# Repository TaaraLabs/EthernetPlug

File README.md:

Ethernet Plug
=============

[WebSite](https://taaralabs.eu/pe1)

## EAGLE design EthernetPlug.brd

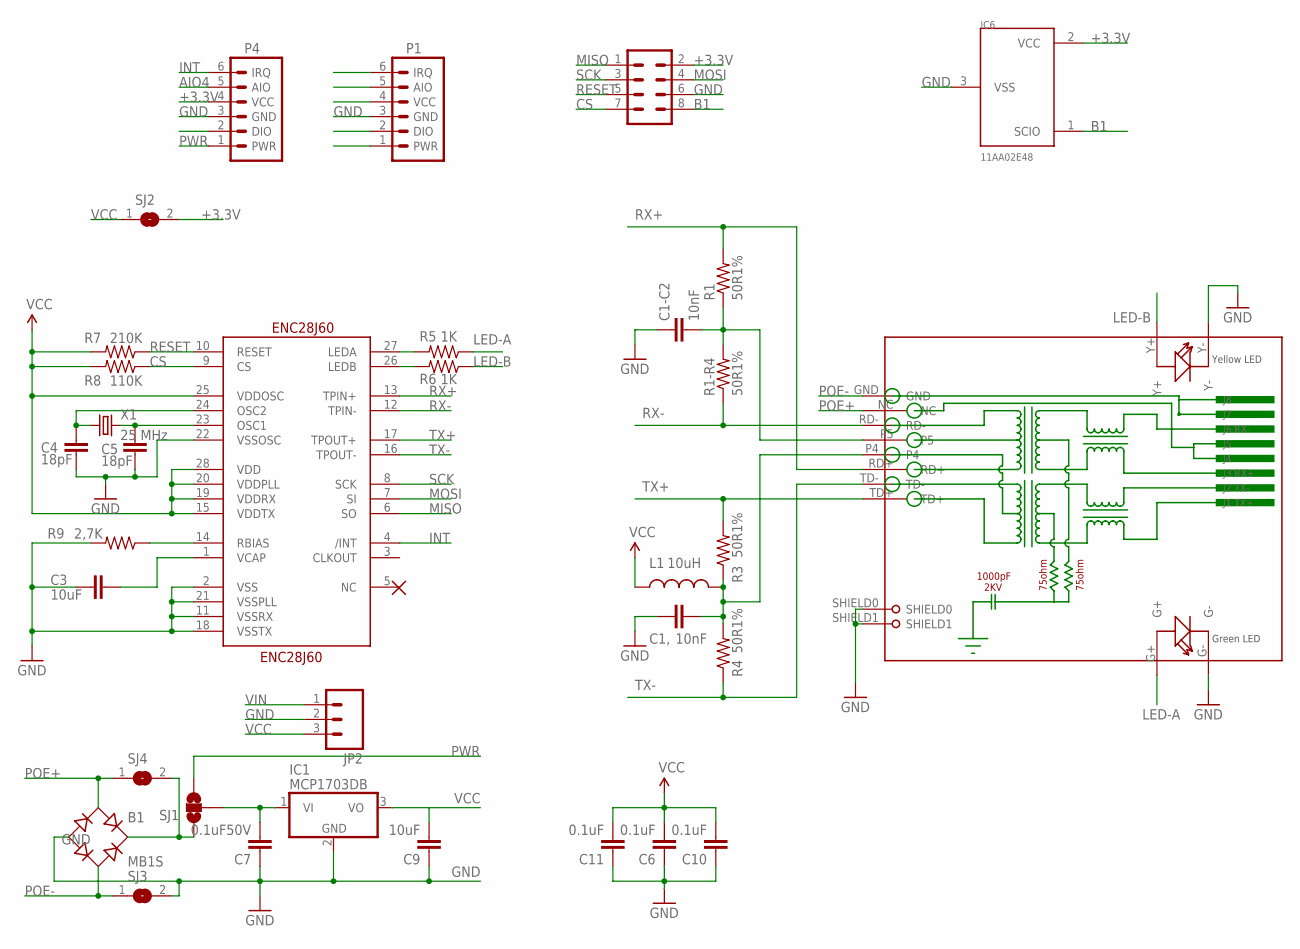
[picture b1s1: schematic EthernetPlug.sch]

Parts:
B1: MB1S; SOIC-4
C1,, C1-C2: 10nF; 0603-CAP
C3, C9: 10uF; 0603-CAP
C4, C5: 18pF; 0603-CAP
C6, C10, C11: 0.1uF; 0603-CAP
C7: 0.1uF50V; 0603-CAP
ENC28J60: ENC28J60; SSOP28DB
IC1: MCP1703DB; SOT223
IC6: 11AA02E48; SOT23
ISP: MA04-2
JP2: M03PTH; 1X03
L1: 10uH; 0603
P1, P4: JEEPORT-FEMALE; 1X06_FEMALE_LOCK.010
R1, R1-R4, R3, R4: 50R1%; 0603-RES
R5, R6: 1K; 0603-RES
R7: 210K; 0603-RES
R8: 110K; 0603-RES
R9: 2,7K; 0603-RES
RJ1: HLJ-6115ANL; HR911105A
SJ1: SOLDERJUMPER_2WAYT; SJ_2
SJ2, SJ3, SJ4: SJ
X1: 25 MHz; CRYSTAL-SMD-3.2X2.5

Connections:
+3.3V: IC6.2 (VCC), ISP.2, P4.4 (VCC), SJ2.2
AIO4: P4.5 (AIO)
B1: IC6.1 (SCIO), ISP.8
CS: ENC28J60.9 (CS), ISP.7, R8.1
GND: B1.-, C1,.1, C1-C2.1, C3.1, C4.1, C5.1, C6.1, C7.1, C9.1, C10.1, C11.1, ENC28J60.2 (VSS), ENC28J60.11 (VSSRX), ENC28J60.18 (VSSTX), ENC28J60.21 (VSSPLL), ENC28J60.22 (VSSOSC), IC1.2 (GND), IC6.3 (VSS), ISP.6, JP2.2, P1.3 (GND), P4.3 (GND), R9.2, RJ1.G-, RJ1.SHIELD0, RJ1.SHIELD1, RJ1.Y-, SJ3.2
INT: ENC28J60.4 (/INT), P4.6 (IRQ)
LED-A: R5.1, RJ1.G+
LED-B: R6.1, RJ1.Y+
MISO: ENC28J60.6 (SO), ISP.1
MOSI: ENC28J60.7 (SI), ISP.4
unnamed: ENC28J60.14 (RBIAS), R9.1
unnamed: ENC28J60.27 (LEDA), R5.2
unnamed: ENC28J60.26 (LEDB), R6.2
unnamed: B1.+, SJ1.1, SJ4.2
unnamed: C4.2, ENC28J60.24 (OSC2), X1.1
unnamed: C5.2, ENC28J60.23 (OSC1), X1.3 (2)
unnamed: C3.2, ENC28J60.1 (VCAP)
POE+: B1.~1 (AC1), RJ1.NC, SJ4.1
POE-: B1.~2 (AC2), RJ1.GND, SJ3.1
PWR: P4.1 (PWR), SJ1.3
RCT: C1-C2.2, R1.1, R1-R4.2, RJ1.P5
RESET: ENC28J60.10 (RESET), ISP.5, R7.1
RX+: ENC28J60.13 (TPIN+), R1.2, RJ1.RD+
RX-: ENC28J60.12 (TPIN-), R1-R4.1, RJ1.RD-
SCK: ENC28J60.8 (SCK), ISP.3
TCT: C1,.2, L1.2, R3.1, R4.2, RJ1.P4
TX+: ENC28J60.17 (TPOUT+), R3.2, RJ1.TD+
TX-: ENC28J60.16 (TPOUT-), R4.1, RJ1.TD-
VCC: C6.2, C9.2, C10.2, C11.2, ENC28J60.15 (VDDTX), ENC28J60.19 (VDDRX), ENC28J60.20 (VDDPLL), ENC28J60.25 (VDDOSC), ENC28J60.28 (VDD), IC1.3 (VO), JP2.3, L1.1, R7.2, R8.2, SJ2.1
VIN: C7.2, IC1.1 (VI), JP2.1, SJ1.2

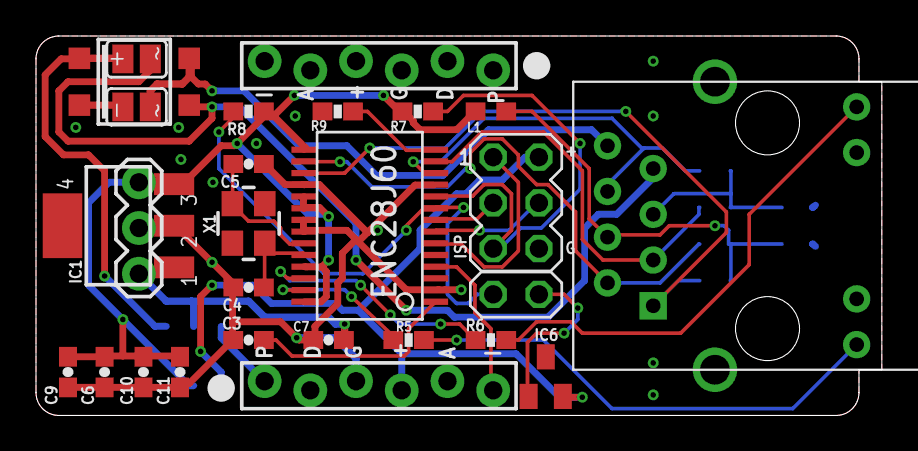
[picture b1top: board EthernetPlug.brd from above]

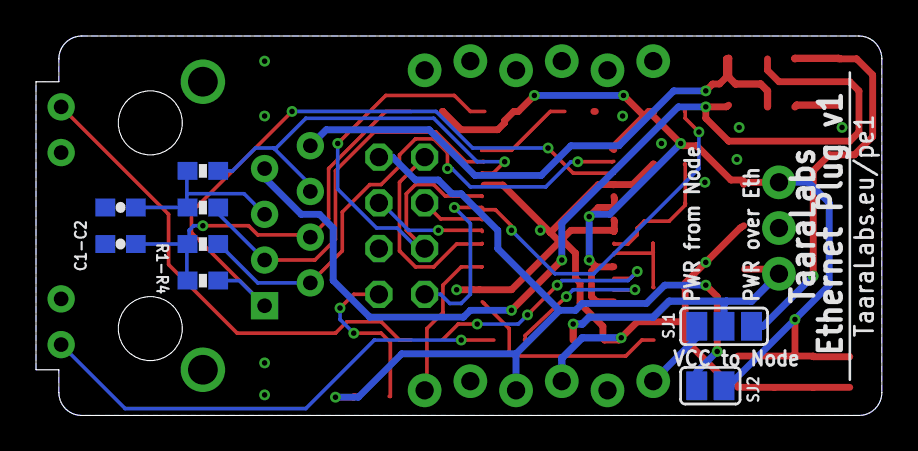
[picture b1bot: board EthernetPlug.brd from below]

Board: 2 copper layers, 47.0 x 21.1 mm, 34 parts (8 on the bottom side), 29 nets.

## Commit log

2015-01-22 :neckbeard: Added .gitattributes & .gitignore files
2015-01-22 EthernetPlug

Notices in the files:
parts and their libraries:
SparkFun: Licensing: CC v3.0 Share-Alike You are welcome to use this library for commercial purposes.
